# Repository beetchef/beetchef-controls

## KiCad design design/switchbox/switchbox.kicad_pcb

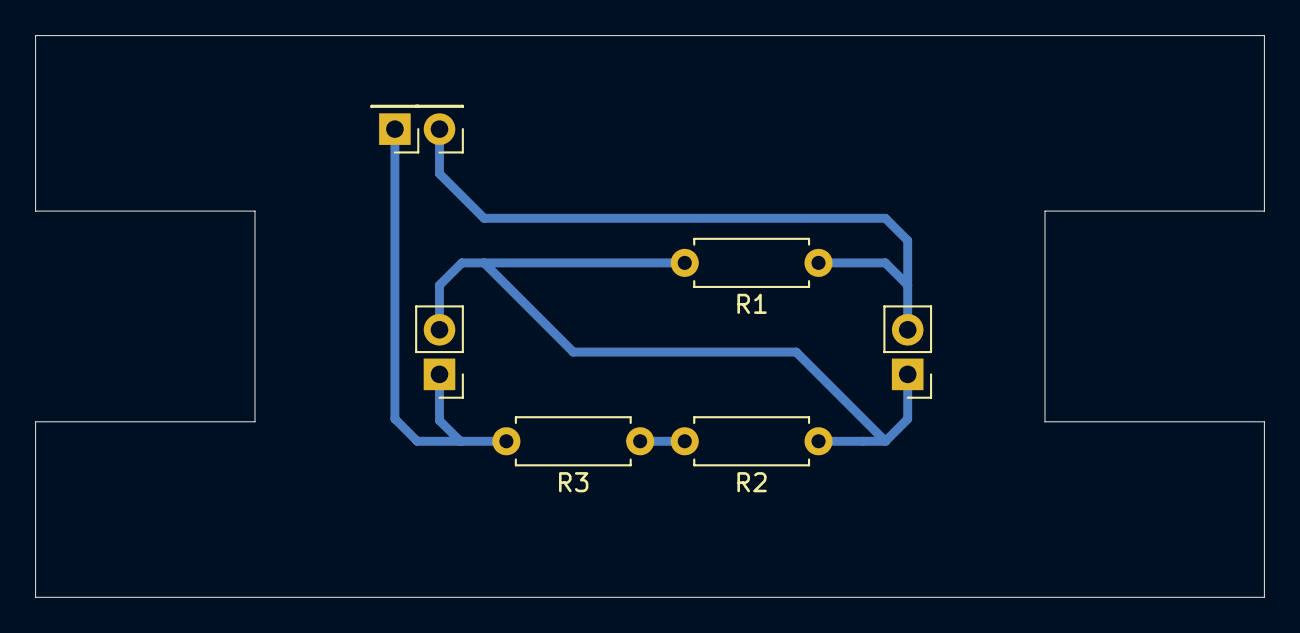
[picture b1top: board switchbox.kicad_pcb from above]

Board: 2 copper layers, 70.0 x 32.0 mm, 7 parts (0 on the bottom side), 4 nets.

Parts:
J1: +5V; PinHeader_1x01_P2.54mm_Vertical
J2: GND; PinHeader_1x01_P2.54mm_Vertical
R1, R2, R3: 10K; R_Axial_DIN0207_L6.3mm_D2.5mm_P7.62mm_Horizontal
SW1: SW1; PinHeader_1x02_P2.54mm_Vertical
SW2: SW2; PinHeader_1x02_P2.54mm_Vertical

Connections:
+5V: J1.1, R3.2, SW2.1
GND: J2.1, R1.1, SW1.2
unnamed: R1.2, R2.1, SW1.1, SW2.2
unnamed: R2.2, R3.1

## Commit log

2019-07-13 intial commit
2019-07-13 changed variable names
2019-07-13 press types added
2019-07-13 printing events to serial port
2019-07-13 Press types (#1)
    * press types added
    * printing events to serial port
2019-07-13 renaming
2019-07-13 implemented digital footswitch
2019-07-13 analog footswitch implemented
2019-07-13 changed footswitch to switchbox
2019-07-14 added include guard
2019-08-17 Refactored analog and digital switch boxes
2019-08-17 Removed keywords.txt
2019-08-17 Corrected typo
2019-08-17 Edited comment
2019-08-17 Added comment
2019-09-05 Refactored switch boxes to inherit from common abstract switch box
2019-09-05 Analog butt (#2)
    * renaming
    * implemented digital footswitch
    * analog footswitch implemented
    * changed footswitch to switchbox
    * added include guard
    * Refactored analog and digital switch boxes
2019-11-07 Adjusted value ranges
2019-12-09 Added kicad projects for designs
2019-12-09 Added .gitignore
2019-12-09 Aligned schema
2019-12-09 Updated .gitignore
2019-12-09 Added design for switchbox PCB
2019-12-31 Proper edge cuts alignment
2019-12-31 Added filled areas
2020-01-03 Updated footprints for wire connectors, angles on tracks changed to 45 degrees
2020-01-03 Updated footprints and front size texts
2020-01-05 Changed width for terminal pins
2020-01-06 Added label to PCB
2020-01-06 Changed label for analog pin terminal
